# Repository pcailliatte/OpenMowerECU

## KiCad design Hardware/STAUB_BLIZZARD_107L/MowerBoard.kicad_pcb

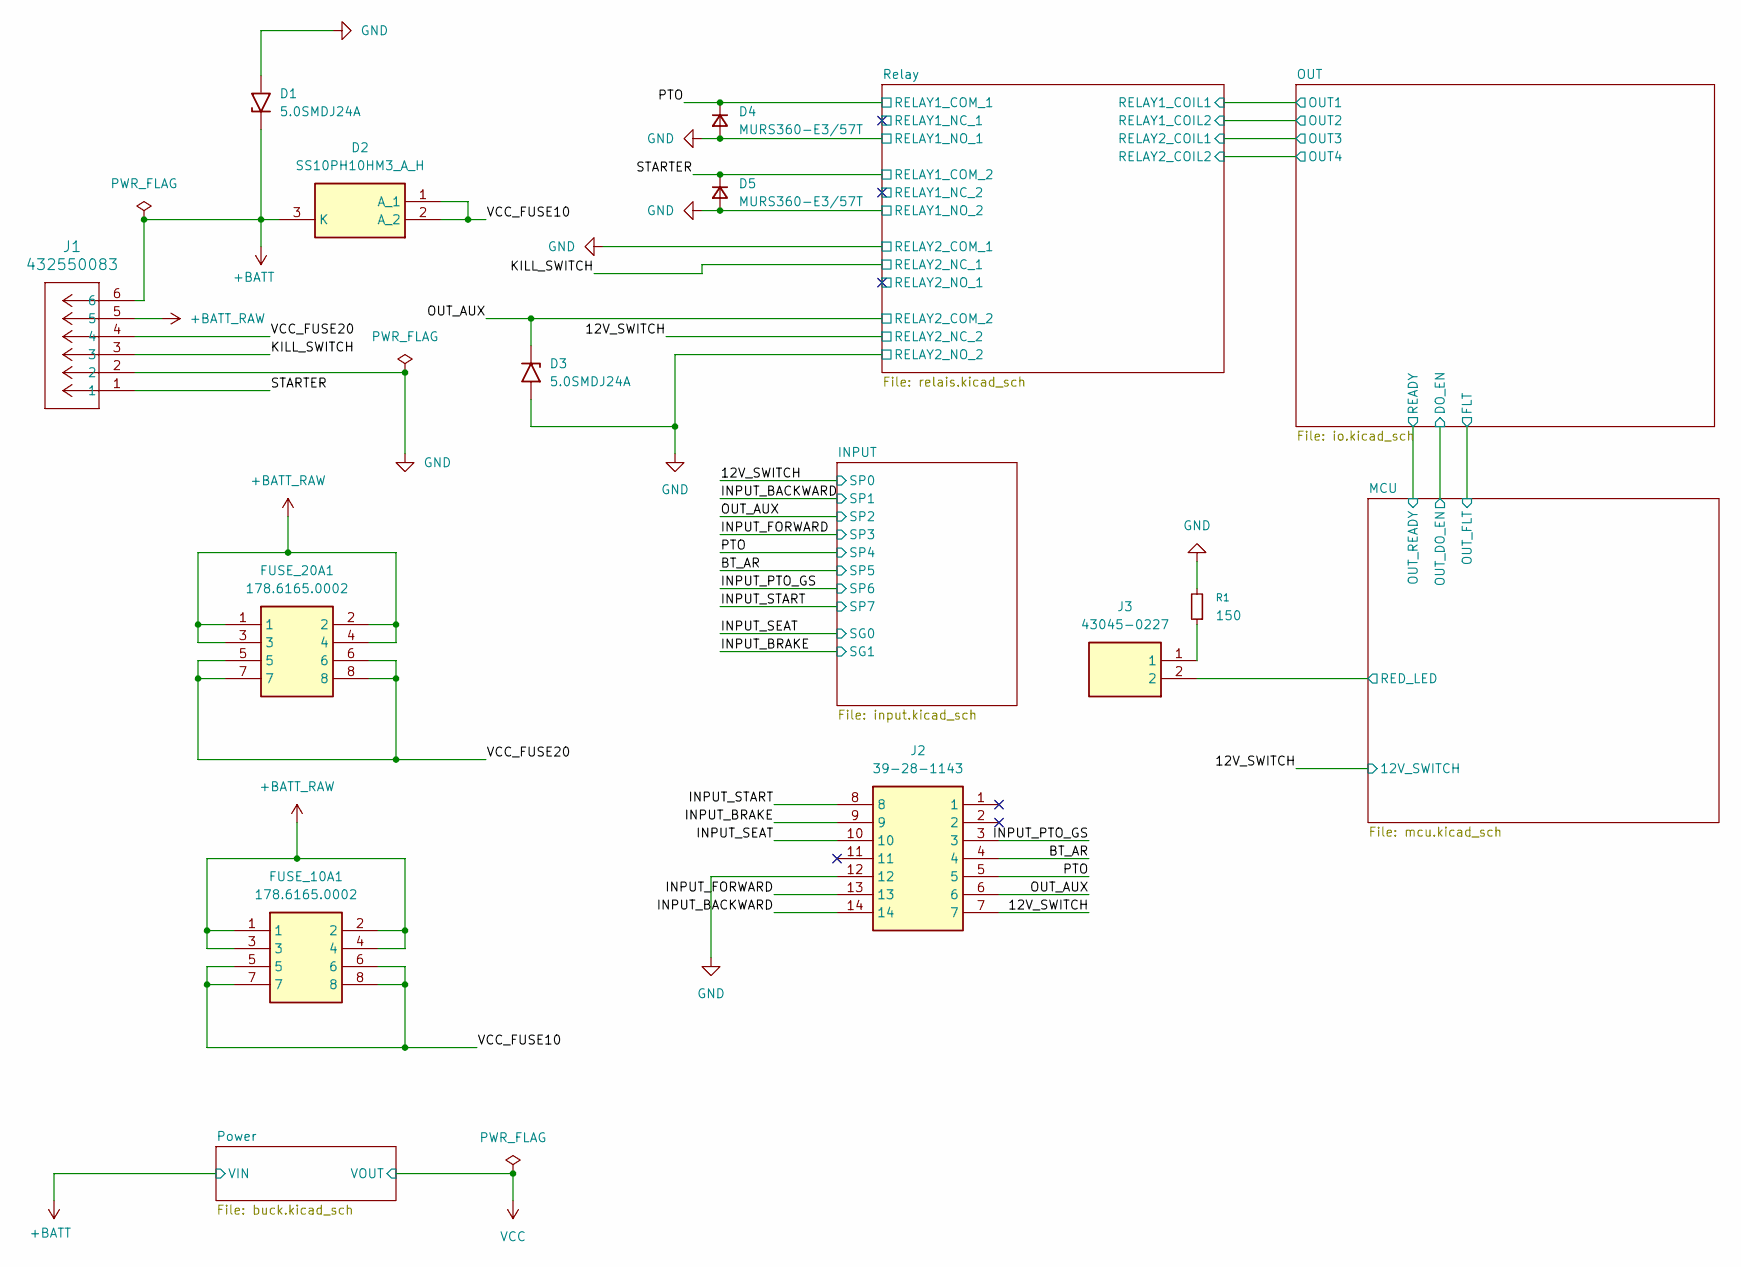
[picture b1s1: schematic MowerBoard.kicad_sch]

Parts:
D1, D3: 5.0SMDJ24A; D_SMC; Mouser Part Number 576-5.0SMDJ24A
D2: SS10PH10HM3_A_H; V10PN50M387A; Mouser Part Number 78-SS10PH10HM3_A/H
D4, D5: MURS360-E3/57T; D_SMC
FUSE_10A1, FUSE_20A1: 178.6165.0002; 17861650002; Mouser Part Number 576-178.6165.0002
J1: 432550083; CONN_SDA_43255-00xx_06_MOL_NO_MARK
J2: 39-28-1143; Mouser Part Number 538-39-28-1143
J3: 43045-0227; 43045-02YY_272829; Mouser Part Number 538-43045-0227
R1: 150; R_0603_1608Metric

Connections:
+BATT: D1.1 (A1), D2.3 (K), J1.6; also elsewhere on the board
+BATT_RAW: FUSE_10A1.1, FUSE_10A1.2, FUSE_10A1.3, FUSE_10A1.4, FUSE_20A1.1, FUSE_20A1.2, FUSE_20A1.3, FUSE_20A1.4, J1.5
/12V_SWITCH: J2.7; also elsewhere on the board
/BT_AR: J2.4; also elsewhere on the board
/INPUT_BACKWARD: J2.14; also elsewhere on the board
/INPUT_BRAKE: J2.9; also elsewhere on the board
/INPUT_FORWARD: J2.13; also elsewhere on the board
/INPUT_PTO_GS: J2.3; also elsewhere on the board
/INPUT_SEAT: J2.10; also elsewhere on the board
/INPUT_START: J2.8; also elsewhere on the board
/KILL_SWITCH: J1.3; also elsewhere on the board
/MCU/RED_LED: J3.2; also elsewhere on the board
/OUT_AUX: D3.1 (A1), J2.6; also elsewhere on the board
/PTO: D4.1 (K), J2.5; also elsewhere on the board
/STARTER: D5.1 (K), J1.1; also elsewhere on the board
/VCC_FUSE10: D2.1 (A_1), D2.2 (A_2), FUSE_10A1.5, FUSE_10A1.6, FUSE_10A1.7, FUSE_10A1.8
/VCC_FUSE20: FUSE_20A1.5, FUSE_20A1.6, FUSE_20A1.7, FUSE_20A1.8, J1.4
GND: D1.2 (A2), D3.2 (A2), D4.2 (A), D5.2 (A), J1.2, J2.12, R1.2; also elsewhere on the board
unnamed: J3.1, R1.1

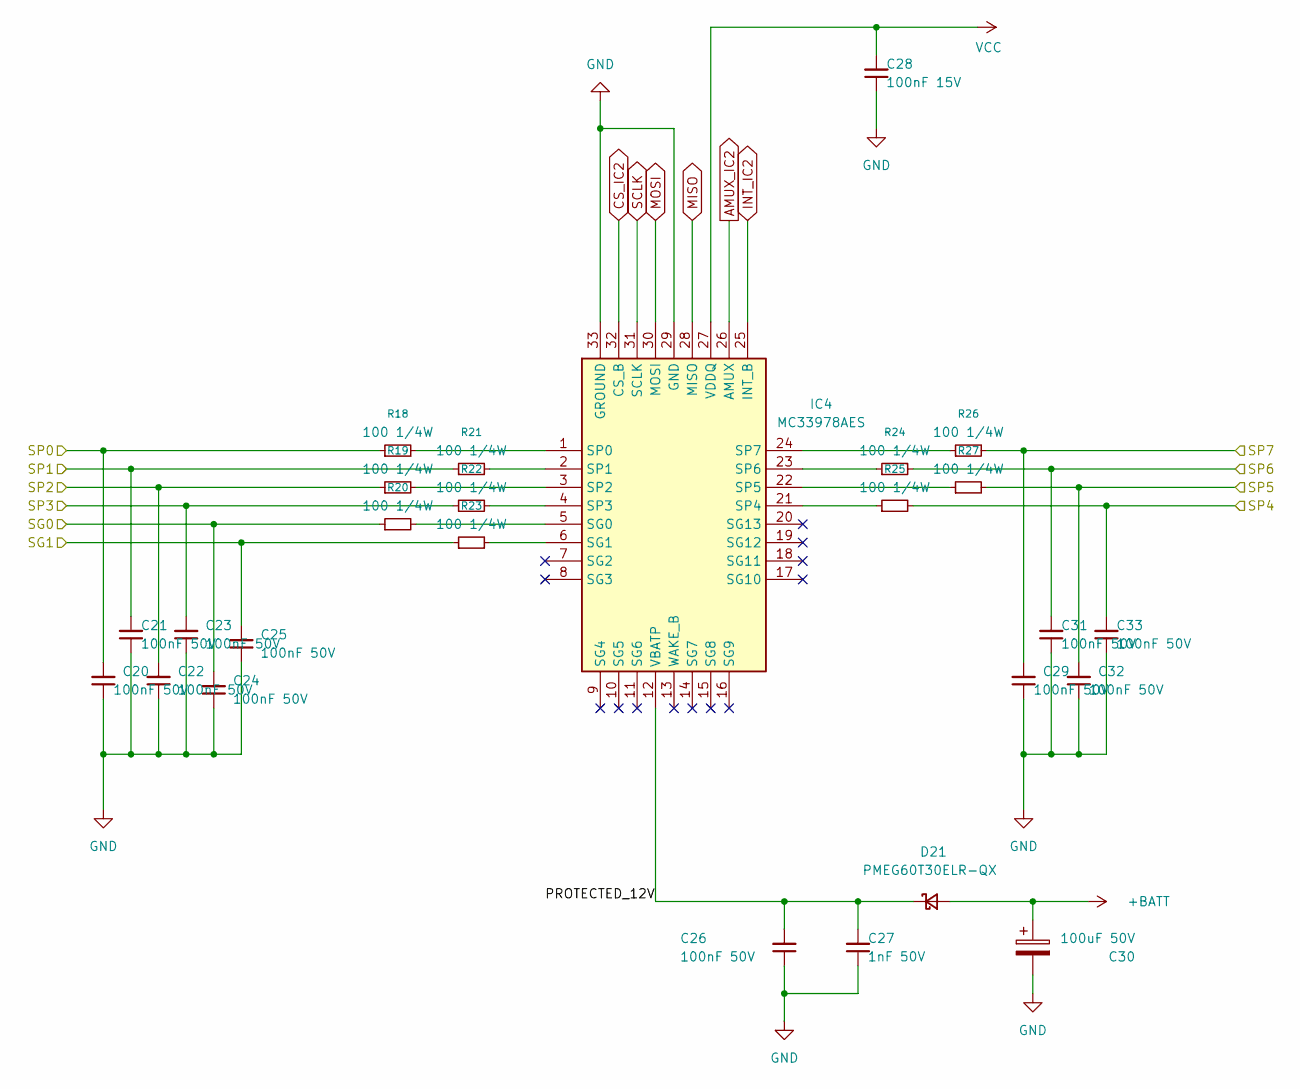
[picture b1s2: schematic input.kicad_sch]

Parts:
C20, C21, C22, C23, C24, C25, C26, C29, C31, C32, C33: 100nF 50V; C_0603_1608Metric
C27: 1nF 50V; C_0402_1005Metric
C28: 100nF 15V; C_0402_1005Metric
C30: 100uF 50V; CP_Elec_8x10
D21: PMEG60T30ELR-QX; Nexperia_CFP3_SOD-123W
IC4: MC33978AES; QFN50P500X500X90-33N-D_Pasta; Mouser Part Number 841-MC33978AES
R18, R19, R20, R21, R22, R23, R24, R25, R26, R27: 100 1/4W; R_0603_1608Metric

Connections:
+BATT: C30.1, D21.2 (A); also elsewhere on the board
/12V_SWITCH: C20.2, R18.1; also elsewhere on the board
/BT_AR: C32.2, R27.2; also elsewhere on the board
/INPUT/PROTECTED_12V: C26.2, C27.2, D21.1 (K), IC4.12 (VBATP)
/INPUT_BACKWARD: C21.2, R21.1; also elsewhere on the board
/INPUT_BRAKE: C25.2, R23.1; also elsewhere on the board
/INPUT_FORWARD: C23.2, R22.1; also elsewhere on the board
/INPUT_PTO_GS: C31.2, R24.2; also elsewhere on the board
/INPUT_SEAT: C24.2, R20.1; also elsewhere on the board
/INPUT_START: C29.2, R26.2; also elsewhere on the board
/OUT_AUX: C22.2, R19.1; also elsewhere on the board
/PTO: C33.2, R25.2; also elsewhere on the board
AMUX_IC2: IC4.26 (AMUX); also elsewhere on the board
CS_IC2: IC4.32 (CS_B); also elsewhere on the board
GND: C20.1, C21.1, C22.1, C23.1, C24.1, C25.1, C26.1, C27.1, C28.1, C29.1, C30.2, C31.1, C32.1, C33.1, IC4.29 (GND), IC4.33 (GROUND); also elsewhere on the board
INT_IC2: IC4.25 (INT_B); also elsewhere on the board
MISO: IC4.28 (MISO); also elsewhere on the board
MOSI: IC4.30 (MOSI); also elsewhere on the board
unnamed: IC4.5 (SG0), R20.2
unnamed: IC4.6 (SG1), R23.2
unnamed: IC4.1 (SP0), R18.2
unnamed: IC4.2 (SP1), R21.2
unnamed: IC4.3 (SP2), R19.2
unnamed: IC4.4 (SP3), R22.2
unnamed: IC4.21 (SP4), R25.1
unnamed: IC4.22 (SP5), R27.1
unnamed: IC4.23 (SP6), R24.1
unnamed: IC4.24 (SP7), R26.1
SCLK: IC4.31 (SCLK); also elsewhere on the board
VCC: C28.2, IC4.27 (VDDQ); also elsewhere on the board

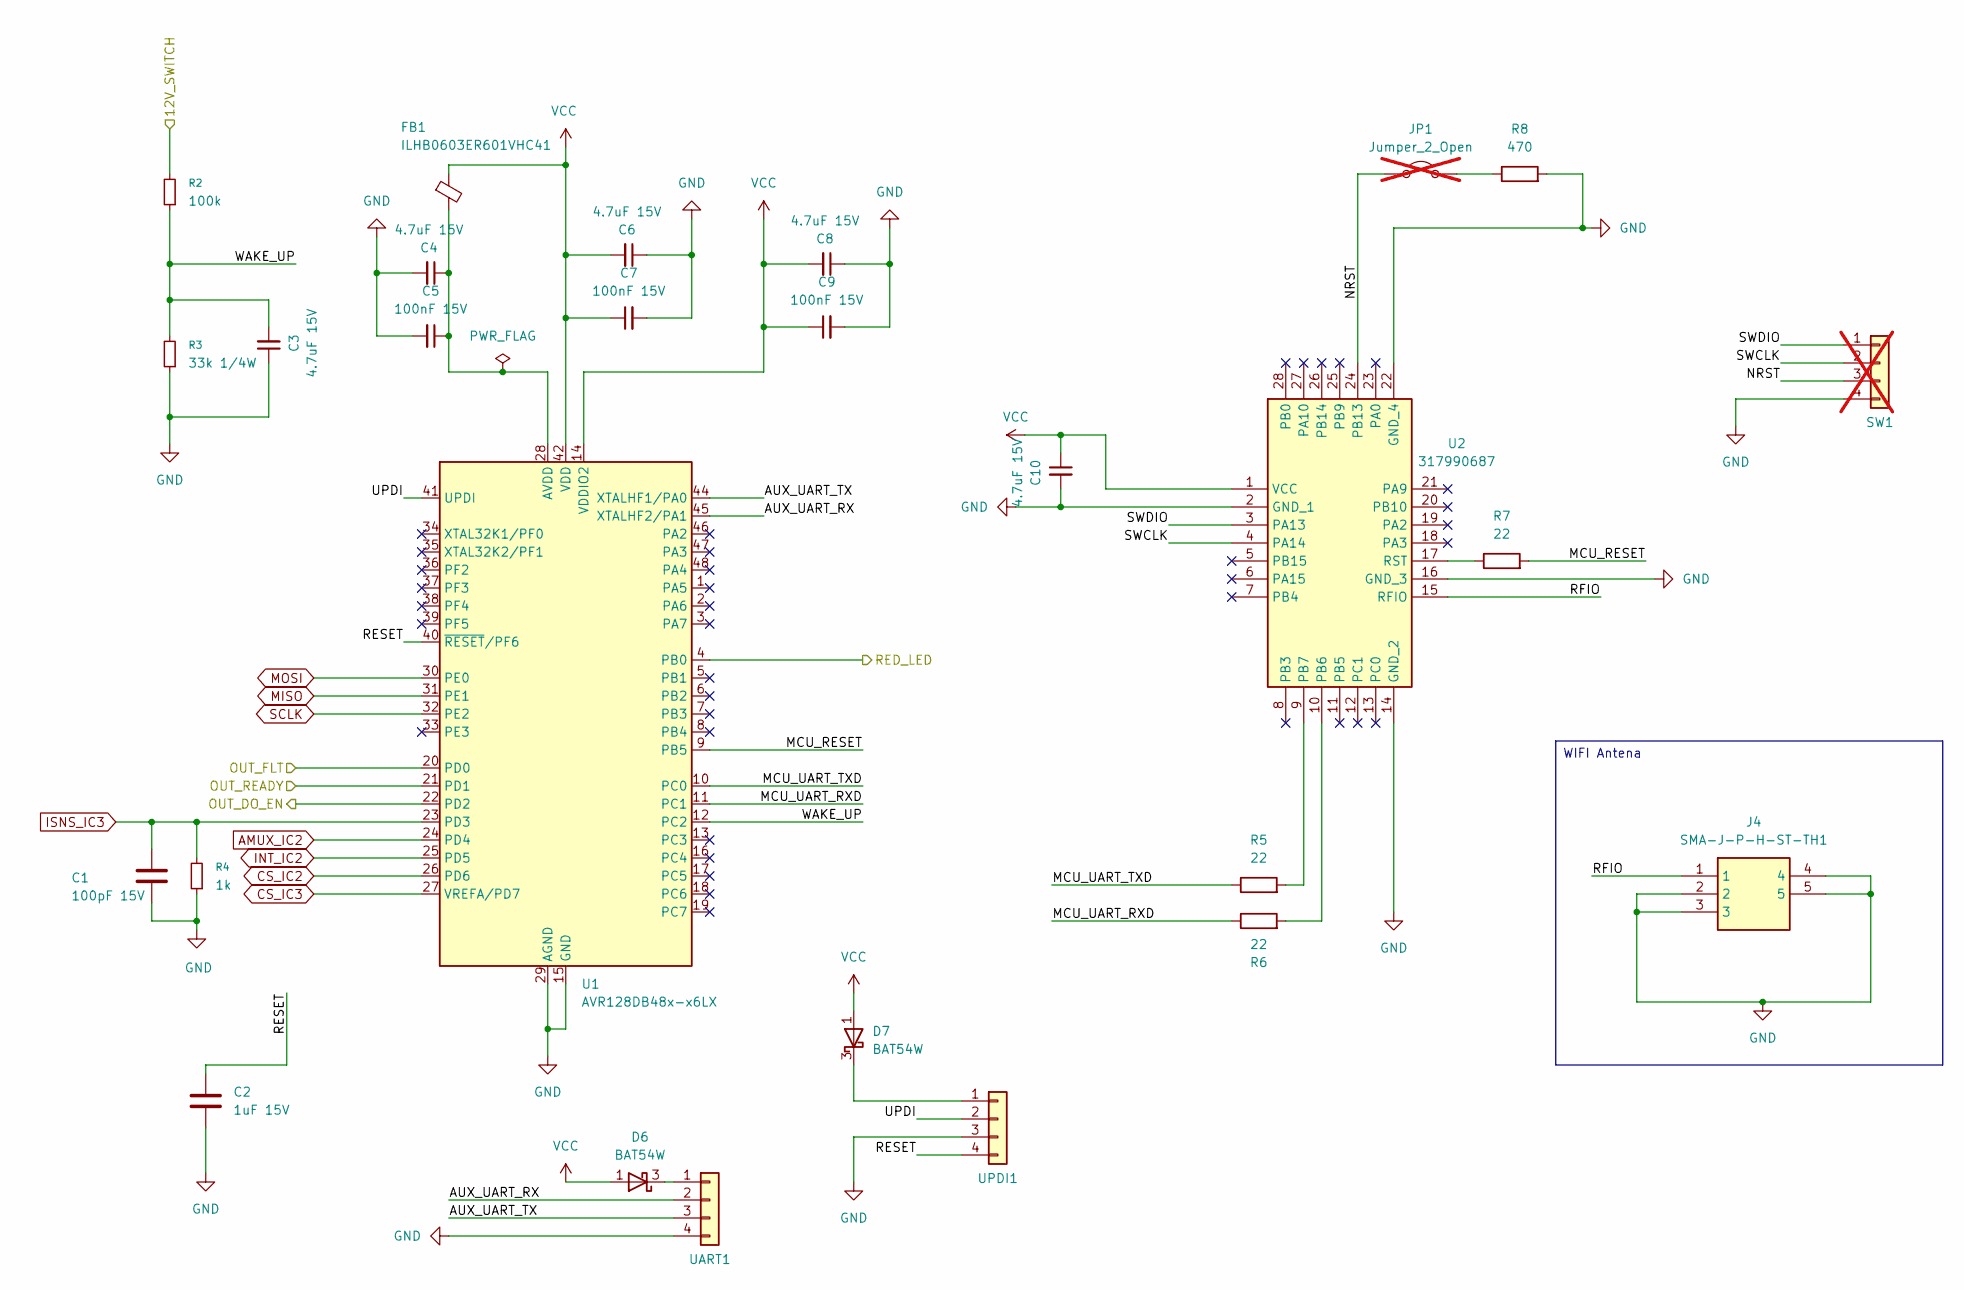
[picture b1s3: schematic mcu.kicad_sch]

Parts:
C1: 100pF 15V; C_0402_1005Metric
C2: 1uF 15V; C_0402_1005Metric
C3, C4, C6, C8, C10: 4.7uF 15V; C_0603_1608Metric
C5, C7, C9: 100nF 15V; C_0402_1005Metric
D6, D7: BAT54W; SOT-323_SC-70
FB1: ILHB0603ER601VHC41; R_0603_1608Metric_Pad0.98x0.95mm_HandSolder
J4: SMA-J-P-H-ST-TH1; SMAJPHSTTH1; Mouser Part Number 200-SMAJPHSTTH1
JP1: Jumper_2_Open; PinHeader_1x02_P2.54mm_Vertical; not fitted
R2: 100k; R_0603_1608Metric
R3: 33k 1/4W; R_0603_1608Metric
R4: 1k; R_0603_1608Metric
R5, R6, R7: 22; R_0603_1608Metric
R8: 470; R_0603_1608Metric
SW1: PinHeader_1x04_P2.54mm_Vertical; not fitted
U1: AVR128DB48x-x6LX; VQFN-48-1EP_6x6mm_P0.4mm_EP4.1x4.1mm
U2: 317990687; Mouser Part Number 713-317990687
UART1: PinHeader_1x04_P2.54mm_Vertical
UPDI1: PinHeader_1x04_P2.54mm_Vertical

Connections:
/12V_SWITCH: R2.2; also elsewhere on the board
/MCU/AUX_UART_RX: U1.45 (XTALHF2/PA1), UART1.2
/MCU/AUX_UART_TX: U1.44 (XTALHF1/PA0), UART1.3
/MCU/MCU_RESET: R7.2, U1.9 (PB5)
/MCU/MCU_UART_RXD: R6.1, U1.11 (PC1)
/MCU/MCU_UART_TXD: R5.1, U1.10 (PC0)
/MCU/NRST: JP1.1 (A), SW1.3, U2.24 (PB13)
/MCU/OUT_FLT: U1.20 (PD0); also elsewhere on the board
/MCU/OUT_READY: U1.21 (PD1); also elsewhere on the board
/MCU/RED_LED: U1.4 (PB0); also elsewhere on the board
/MCU/RESET: C2.1, U1.40 (~RESET/PF6), UPDI1.4
/MCU/RFIO: J4.1, U2.15 (RFIO)
/MCU/SWCLK: SW1.2, U2.4 (PA14)
/MCU/SWDIO: SW1.1, U2.3 (PA13)
/MCU/UPDI: U1.41 (UPDI), UPDI1.2
/MCU/WAKE_UP: C3.2, R2.1, R3.2, U1.12 (PC2)
/OUT/DO_EN: U1.22 (PD2); also elsewhere on the board
AMUX_IC2: U1.24 (PD4); also elsewhere on the board
CS_IC2: U1.26 (PD6); also elsewhere on the board
CS_IC3: U1.27 (VREFA/PD7); also elsewhere on the board
GND: C1.2, C2.2, C3.1, C4.2, C5.2, C6.1, C7.2, C8.1, C9.2, C10.2, J4.2, J4.3, J4.4, J4.5, R3.1, R4.1, R8.2, SW1.4, U1.15 (GND), U1.29 (AGND), U1.43 (GND), U1.49 (GND), U2.2 (GND_1), U2.14 (GND_2), U2.16 (GND_3), U2.22 (GND_4), UART1.4, UPDI1.3; also elsewhere on the board
INT_IC2: U1.25 (PD5); also elsewhere on the board
ISNS_IC3: C1.1, R4.2, U1.23 (PD3); also elsewhere on the board
MISO: U1.31 (PE1); also elsewhere on the board
MOSI: U1.30 (PE0); also elsewhere on the board
unnamed: D6.3 (K), UART1.1
unnamed: D7.3 (K), UPDI1.1
unnamed: JP1.2 (B), R8.1
unnamed: C4.1, C5.1, FB1.2, U1.28 (AVDD)
unnamed: R6.2, U2.10 (PB6)
unnamed: R5.2, U2.9 (PB7)
unnamed: R7.1, U2.17 (RST)
SCLK: U1.32 (PE2); also elsewhere on the board
VCC: C6.2, C7.1, C8.2, C9.1, C10.1, D6.1 (A), D7.1 (A), FB1.1, U1.14 (VDDIO2), U1.42 (VDD), U2.1 (VCC); also elsewhere on the board

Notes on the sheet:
WIFI Antena

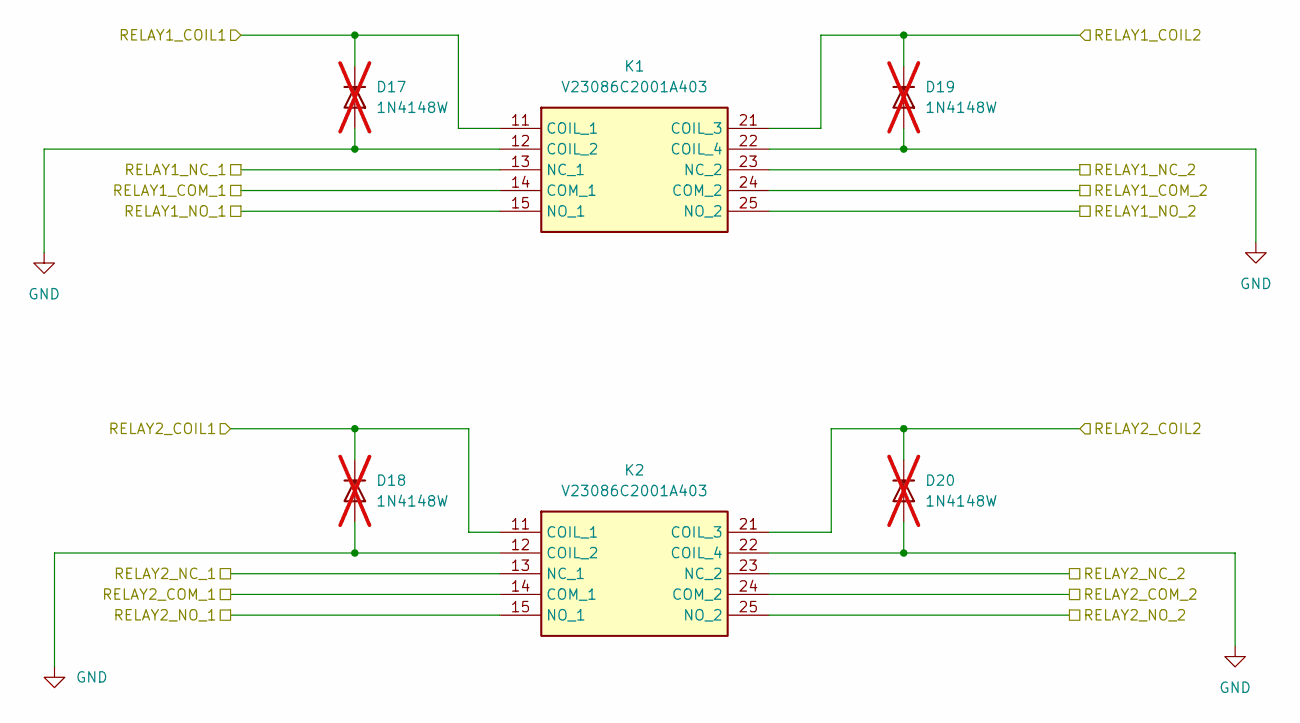
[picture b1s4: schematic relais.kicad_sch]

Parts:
D17, D18, D19, D20: 1N4148W; D_SOD-123; not fitted
K1, K2: V23086C2001A403; Mouser Part Number 571-1413009-9

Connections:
/12V_SWITCH: K2.23 (NC_2); also elsewhere on the board
/KILL_SWITCH: K2.13 (NC_1); also elsewhere on the board
/OUT/OUT1: D17.1 (K), K1.11 (COIL_1); also elsewhere on the board
/OUT/OUT2: D19.1 (K), K1.21 (COIL_3); also elsewhere on the board
/OUT/OUT3: D18.1 (K), K2.11 (COIL_1); also elsewhere on the board
/OUT/OUT4: D20.1 (K), K2.21 (COIL_3); also elsewhere on the board
/OUT_AUX: K2.24 (COM_2); also elsewhere on the board
/PTO: K1.14 (COM_1); also elsewhere on the board
/Relay/RELAY1_NC_1: K1.13 (NC_1)
/Relay/RELAY1_NC_2: K1.23 (NC_2)
/Relay/RELAY2_NO_1: K2.15 (NO_1)
/STARTER: K1.24 (COM_2); also elsewhere on the board
GND: D17.2 (A), D18.2 (A), D19.2 (A), D20.2 (A), K1.12 (COIL_2), K1.15 (NO_1), K1.22 (COIL_4), K1.25 (NO_2), K2.12 (COIL_2), K2.14 (COM_1), K2.22 (COIL_4), K2.25 (NO_2); also elsewhere on the board

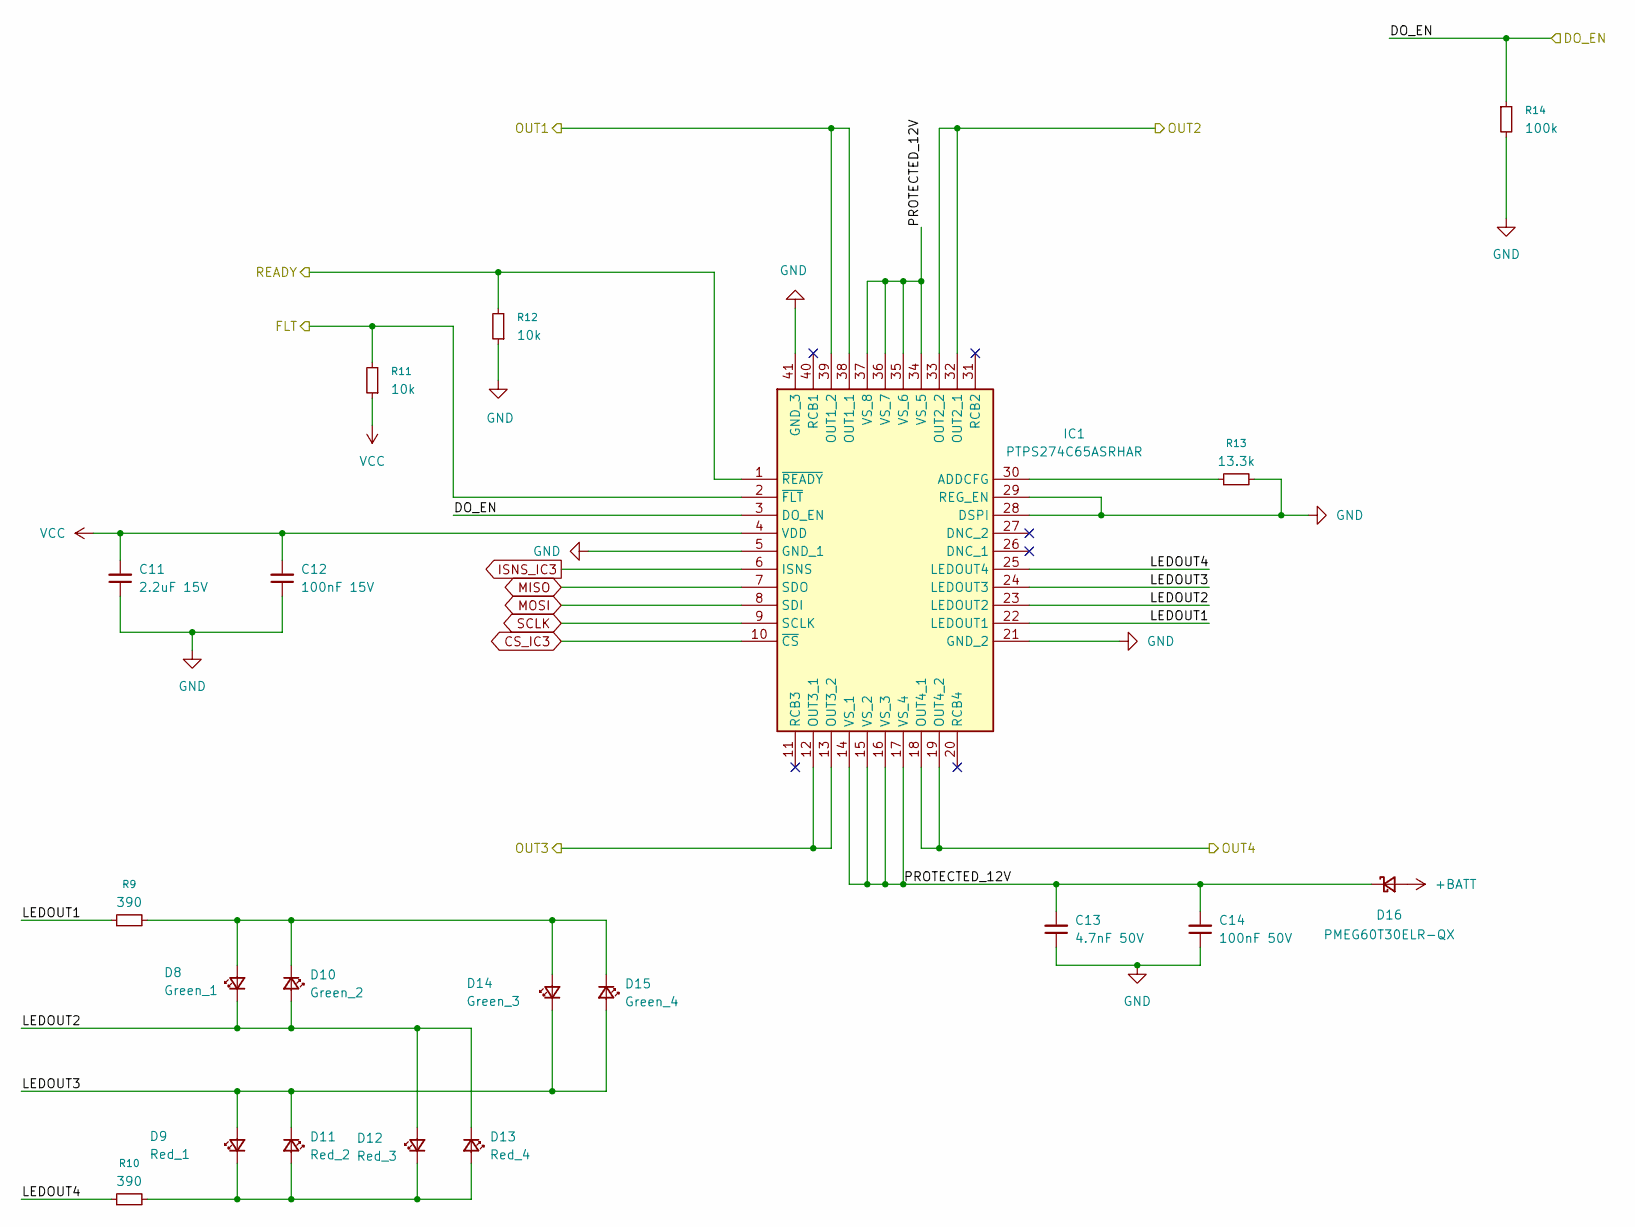
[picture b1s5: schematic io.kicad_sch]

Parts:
C11: 2.2uF 15V; C_0603_1608Metric
C12: 100nF 15V; C_0402_1005Metric
C13: 4.7nF 50V; C_0402_1005Metric
C14: 100nF 50V; C_0402_1005Metric
D8: Green_1; LED_0603_1608Metric
D9: Red_1; LED_0603_1608Metric
D10: Green_2; LED_0603_1608Metric
D11: Red_2; LED_0603_1608Metric
D12: Red_3; LED_0603_1608Metric
D13: Red_4; LED_0603_1608Metric
D14: Green_3; LED_0603_1608Metric
D15: Green_4; LED_0603_1608Metric
D16: PMEG60T30ELR-QX; Nexperia_CFP3_SOD-123W
IC1: PTPS274C65ASRHAR; QFN50P600X600X100-41N-D_pasta; Manufacturer_Part_Number PTPS274C65ASRHAR
R9, R10: 390; R_0603_1608Metric
R11, R12: 10k; R_0603_1608Metric
R13: 13.3k; R_0603_1608Metric
R14: 100k; R_0603_1608Metric

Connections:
+BATT: D16.2 (A); also elsewhere on the board
/MCU/OUT_FLT: IC1.2 (~FLT), R11.2; also elsewhere on the board
/MCU/OUT_READY: IC1.1 (~READY), R12.2; also elsewhere on the board
/OUT/DO_EN: IC1.3 (DO_EN), R14.1; also elsewhere on the board
/OUT/LEDOUT1: IC1.22 (LEDOUT1), R9.1
/OUT/LEDOUT2: D8.1 (K), D10.2 (A), D12.2 (A), D13.1 (K), IC1.23 (LEDOUT2)
/OUT/LEDOUT3: D9.2 (A), D11.1 (K), D14.1 (K), D15.2 (A), IC1.24 (LEDOUT3)
/OUT/LEDOUT4: IC1.25 (LEDOUT4), R10.1
/OUT/OUT1: IC1.38 (OUT1_1), IC1.39 (OUT1_2); also elsewhere on the board
/OUT/OUT2: IC1.32 (OUT2_1), IC1.33 (OUT2_2); also elsewhere on the board
/OUT/OUT3: IC1.12 (OUT3_1), IC1.13 (OUT3_2); also elsewhere on the board
/OUT/OUT4: IC1.18 (OUT4_1), IC1.19 (OUT4_2); also elsewhere on the board
/OUT/PROTECTED_12V: C13.2, C14.2, D16.1 (K), IC1.14 (VS_1), IC1.15 (VS_2), IC1.16 (VS_3), IC1.17 (VS_4), IC1.34 (VS_5), IC1.35 (VS_6), IC1.36 (VS_7), IC1.37 (VS_8)
CS_IC3: IC1.10 (~CS); also elsewhere on the board
GND: C11.1, C12.1, C13.1, C14.1, IC1.5 (GND_1), IC1.21 (GND_2), IC1.28 (DSPI), IC1.29 (REG_EN), IC1.41 (GND_3), R12.1, R13.2, R14.2; also elsewhere on the board
ISNS_IC3: IC1.6 (ISNS); also elsewhere on the board
MISO: IC1.7 (SDO); also elsewhere on the board
MOSI: IC1.8 (SDI); also elsewhere on the board
unnamed: D8.2 (A), D10.1 (K), D14.2 (A), D15.1 (K), R9.2
unnamed: D9.1 (K), D11.2 (A), D12.1 (K), D13.2 (A), R10.2
unnamed: IC1.30 (ADDCFG), R13.1
SCLK: IC1.9 (SCLK); also elsewhere on the board
VCC: C11.2, C12.2, IC1.4 (VDD), R11.1; also elsewhere on the board

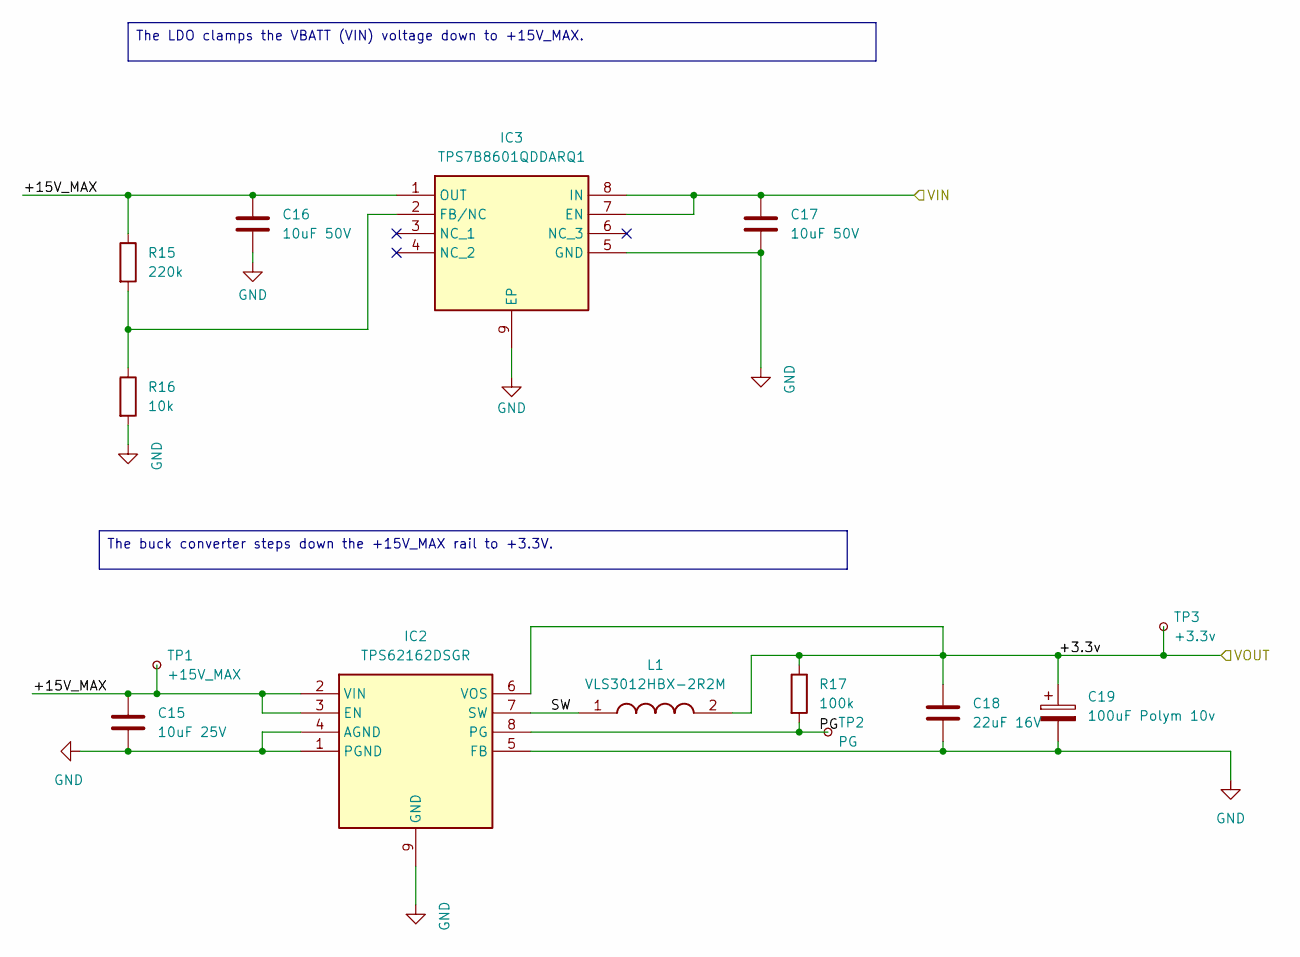
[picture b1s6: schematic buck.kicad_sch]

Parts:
C15: 10uF 25V; C_0805_2012Metric
C16, C17: 10uF 50V; C_1206_3216Metric
C18: 22uF 16V; C_0805_2012Metric
C19: 100uF Polym 10v; CP_Elec_6.3x5.7
IC2: TPS62162DSGR; SON50P200X200X80-9N; Mouser Part Number 595-TPS62162DSGR
IC3: TPS7B8601QDDARQ1; SOIC127P600X170-9N_pasta; Mouser Part Number 595-TPS7B8601QDDARQ1
L1: VLS3012HBX-2R2M; VLS3012; Mouser Part Number 810-VLS3012HBX-2R2M
R15: 220k; R_0603_1608Metric
R16: 10k; R_0603_1608Metric
R17: 100k; R_0603_1608Metric
TP1: +15V_MAX; TestPoint_Pad_1.0x1.0mm
TP2: PG; TestPoint_Pad_1.0x1.0mm
TP3: +3.3v; TestPoint_Pad_1.0x1.0mm

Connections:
+BATT: C17.1, IC3.7 (EN), IC3.8 (IN); also elsewhere on the board
/Power/+15V_MAX: C15.1, C16.1, IC2.2 (VIN), IC2.3 (EN), IC3.1 (OUT), R15.1, TP1.1 (1_1)
/Power/PG: IC2.8 (PG), R17.2, TP2.1 (1_1)
/Power/SW: IC2.7 (SW), L1.1
GND: C15.2, C16.2, C17.2, C18.2, C19.2, IC2.1 (PGND), IC2.4 (AGND), IC2.5 (FB), IC2.9 (GND), IC3.5 (GND), IC3.9 (EP), R16.2; also elsewhere on the board
unnamed: IC3.2 (FB/NC), R15.2, R16.1
VCC: C18.1, C19.1, IC2.6 (VOS), L1.2, R17.1, TP3.1 (1_1); also elsewhere on the board

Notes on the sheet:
The buck converter steps down the +15V_MAX rail to +3.3V.
The LDO clamps the VBATT (VIN) voltage down to +15V_MAX.

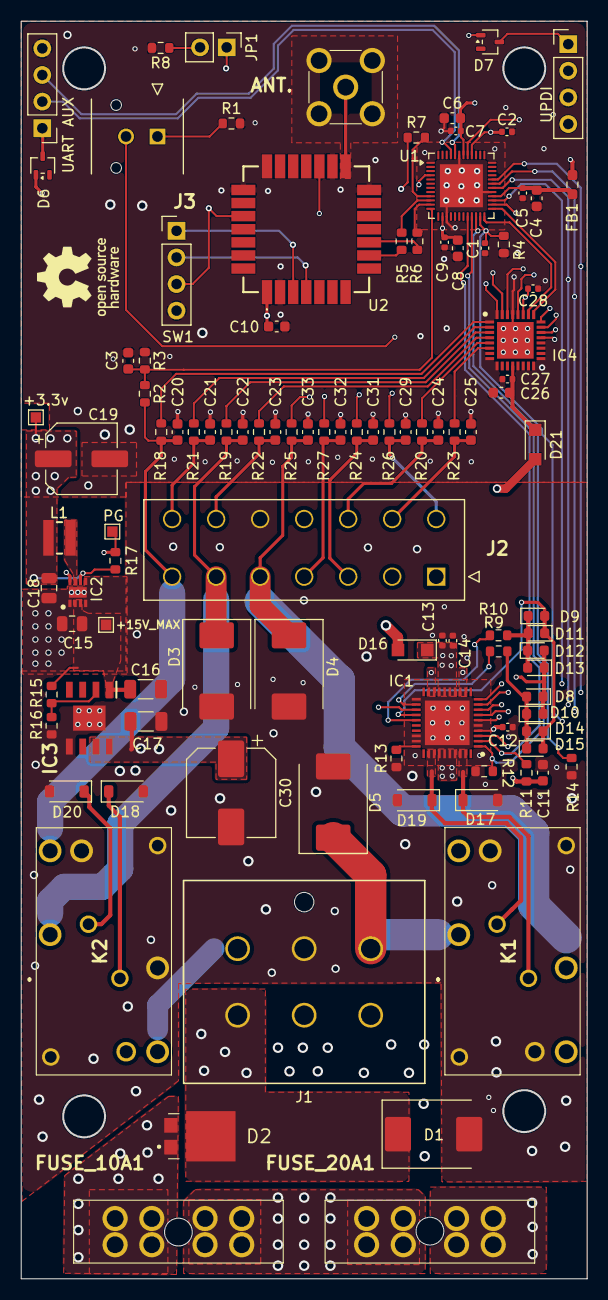
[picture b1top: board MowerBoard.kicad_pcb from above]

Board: 4 copper layers, 54.0 x 120.0 mm, 104 parts (0 on the bottom side), 77 nets.
